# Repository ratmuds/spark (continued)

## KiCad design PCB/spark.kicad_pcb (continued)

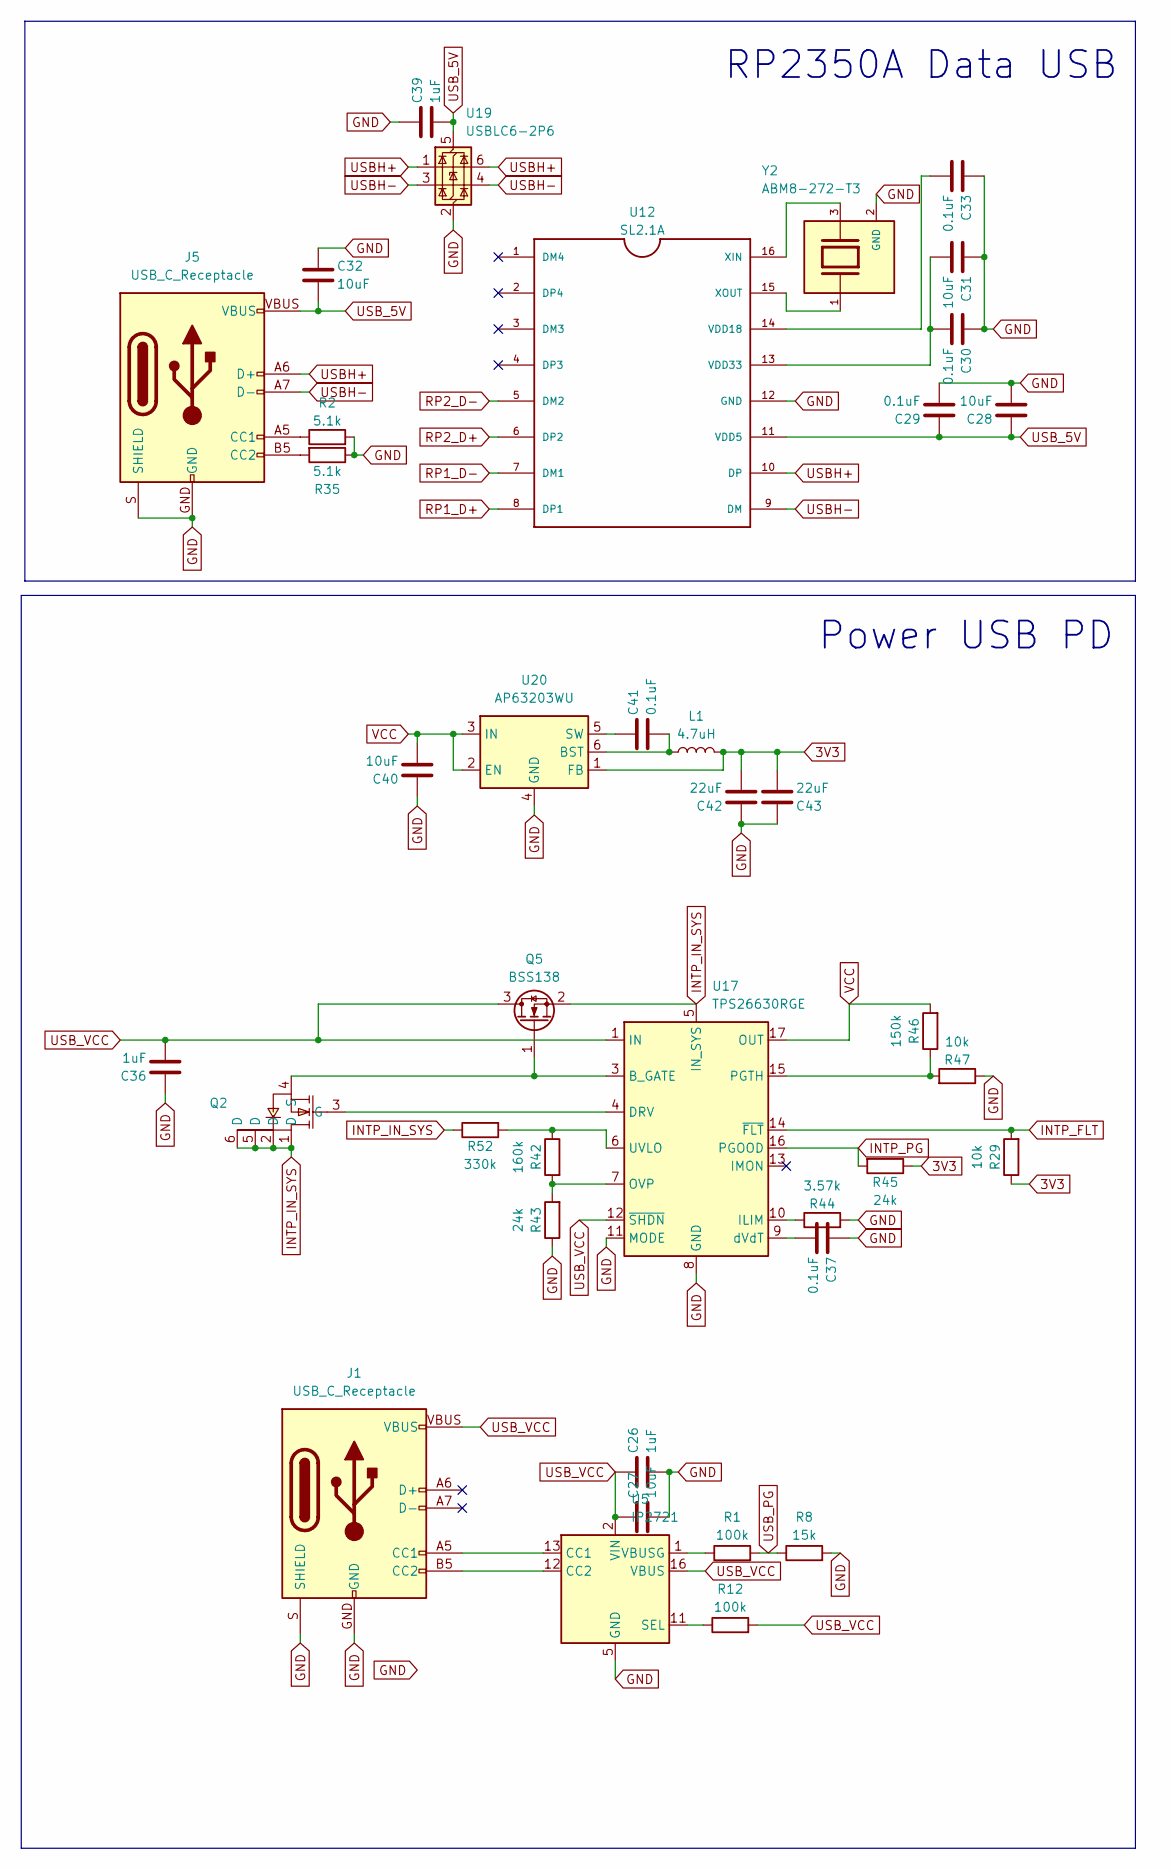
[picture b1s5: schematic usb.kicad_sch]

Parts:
C26, C36, C39: 1uF; C_0402_1005Metric; MPN CL05A105KA5NQNC
C27, C28, C31, C32, C40: 10uF; C_0805_2012Metric; MPN CL21A106KAYNNNE
C29, C30, C33, C37, C41: 0.1uF; C_0402_1005Metric; MPN CL05B104KB54PNC
C42, C43: 22uF; C_0805_2012Metric; MPN CL21A226MAQNNNE
J1, J5: USB_C_Receptacle; USB-C_16; MPN TYPE-C-31-M-12
L1: 4.7uH; L_TechFuse_SL0420; MPN SRP4020TA-4R7M
Q2: STT6N3LLH6_C3021100; SOT-23-6_L2.9-W1.6-P0.95-LS2.8-BR; MPN STT6N3LLH6; LCSC Part C3021100
Q5: BSS138; SOT-23; MPN BSS138
R1, R12: 100k; R_0402_1005Metric; MPN 0402WGF1003TCE
R2, R35: 5.1k; R_0402_1005Metric; MPN 0402WGF5101TCE
R8: 15k; R_0402_1005Metric; MPN 0402WGF1502TCE
R29, R47: 10k; R_0402_1005Metric; MPN 0402WGF1002TCE
R42: 160k; R_0603_1608Metric; MPN 0603WAF1603T5E
R43, R45: 24k; R_0402_1005Metric; MPN 0402WGF2402TCE
R44: 3.57k; R_0603_1608Metric; MPN 0603WAF3601T5E
R46: 150k; R_0402_1005Metric; MPN 0402WGF1503TCE
R52: 330k; R_0402_1005Metric; MPN 0402WGF3303TCE
U5: IP2721; TSSOP-16_4.4x5mm_P0.65mm; MPN IP2721
U12: SL2.1A; SO16; MPN SL2.1A
U17: TPS26630RGE; Texas_RGE0024H_VQFN-24-1EP_4x4mm_P0.5mm_EP2.7x2.7mm_Thermal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; MPN TPS26630RGER
U19: USBLC6-2P6; SOT-666; MPN USBLC6-2P6
U20: AP63203WU; TSOT-23-6; MPN AP63203WU-7
Y2: ABM8-272-T3; XTAL_ABM8-272-T3; PARTREV 07-29-20

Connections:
3V3: C42.1, C43.1, L1.2, R29.1, R45.1, U20.1 (FB); also elsewhere on the board
GND: C26.1, C27.1, C28.1, C29.1, C30.2, C31.2, C32.2, C33.2, C36.2, C37.2, C39.2, C40.2, C42.2, C43.2, J1.GND, J1.S (SHIELD), J5.GND, J5.S (SHIELD), R2.2, R8.2, R35.1, R43.1, R44.2, R47.1, U5.5 (GND), U12.12 (GND), U17.8 (GND), U17.11 (MODE), U17.25 (GND), U19.2 (GND), U20.4 (GND), Y2.2 (GND), Y2.4 (GND); also elsewhere on the board
INTP_FLT: R29.2, U17.14 (~FLT); also elsewhere on the board
INTP_IN_SYS: Q2.1 (D), Q2.2 (D), Q2.5 (D), Q2.6 (D), Q5.2 (S), R52.1, U17.5 (IN_SYS)
INTP_PG: R45.2, U17.16 (PGOOD)
unnamed: J1.A5 (CC1), U5.13 (CC1)
unnamed: J1.B5 (CC2), U5.12 (CC2)
unnamed: J5.A5 (CC1), R2.1
unnamed: J5.B5 (CC2), R35.2
unnamed: Q2.3 (G), U17.4 (DRV)
unnamed: Q2.4 (S), Q5.1 (G), U17.3 (B_GATE)
unnamed: R12.1, U5.11 (SEL)
unnamed: R1.1, U5.1 (VBUSG)
unnamed: C33.1, U12.14 (VDD18)
unnamed: C30.1, C31.1, U12.13 (VDD33)
unnamed: U12.16 (XIN), Y2.3
unnamed: U12.15 (XOUT), Y2.1
unnamed: R44.1, U17.10 (ILIM)
unnamed: R42.2, R43.2, U17.7 (OVP)
unnamed: R46.1, R47.2, U17.15 (PGTH)
unnamed: R42.1, R52.2, U17.6 (UVLO)
unnamed: C37.1, U17.9 (dVdT)
unnamed: C41.1, L1.1, U20.6 (BST)
unnamed: C41.2, U20.5 (SW)
RP1_D+: U12.8 (DP1); also elsewhere on the board
RP1_D-: U12.7 (DM1); also elsewhere on the board
RP2_D+: U12.6 (DP2); also elsewhere on the board
RP2_D-: U12.5 (DM2); also elsewhere on the board
USBH+: J5.A6 (D+), J5.B6 (D+), U12.10 (DP), U19.1 (I/O1), U19.6 (I/O1)
USBH-: J5.A7 (D-), J5.B7 (D-), U12.9 (DM), U19.3 (I/O2), U19.4 (I/O2)
USB_5V: C28.2, C29.2, C32.1, C39.1, J5.VBUS, U12.11 (VDD5), U19.5 (VBUS)
USB_PG: R1.2, R8.1; also elsewhere on the board
USB_VCC: C26.2, C27.2, C36.1, J1.VBUS, Q5.3 (D), R12.2, U5.2 (VIN), U5.16 (VBUS), U17.1 (IN), U17.2 (IN), U17.12 (~SHDN)
VCC: C40.1, R46.2, U17.17 (OUT), U17.18 (OUT), U20.2 (EN), U20.3 (IN); also elsewhere on the board

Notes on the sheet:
Power USB PD
RP2350A Data USB

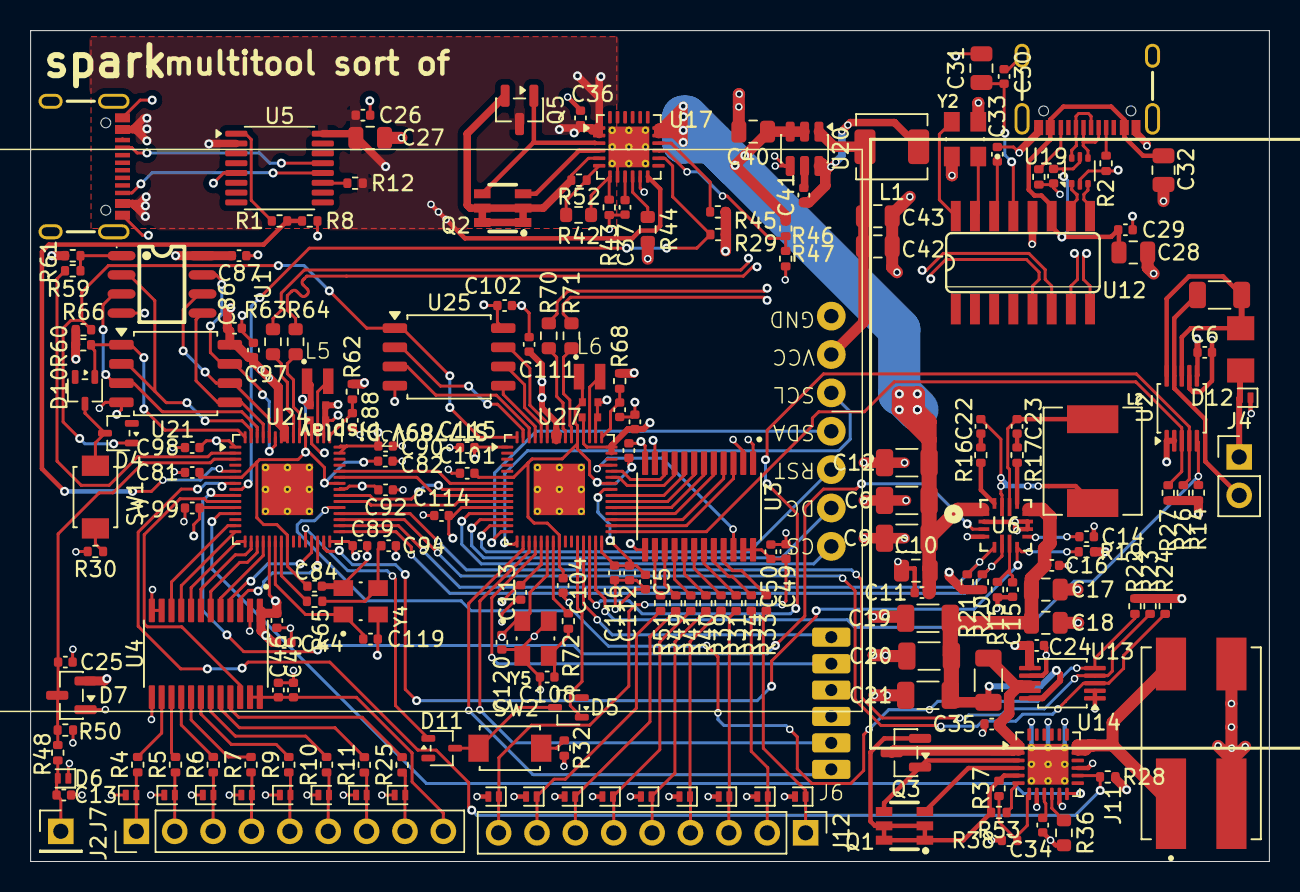
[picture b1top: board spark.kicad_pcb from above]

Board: 4 copper layers, 82.0 x 55.0 mm, 202 parts (0 on the bottom side), 170 nets.

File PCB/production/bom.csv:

Designator,Footprint,Quantity,Value,LCSC Part #
C10,0805,1,22uF 25V,CL21A226MAQNNNE
"C100, C103, C104, C105, C82, C83, C85, C88",0402,8,4.7uF,CL05A475MP5NRNC
"C101, C102, C106, C110, C111, C112, C113, C114, C115, C116, C24, C25, C29, C30, C33, C34, C37, C41, C44, C45, C49, C5, C81, C84, C86, C87, C89, C90, C91, C92, C97, C98, C99",0402,33,0.1uF,CL05B104KB54PNC
"C108, C119, C120, C94",0402,4,15pF,0402CG150J500NT
"C11, C16, C22, C23, C6",0402,5,0.1uF 25V,CL05B104KB54PNC
"C12, C19, C20, C21, C8, C9",1206,6,47uF 25V,C3216X5R1E476MTJ00E
C13,0402,1,100pF C0G/NP0,0402CG101J500NT
"C14, C26, C35, C36, C39, C46, C50",0402,7,1uF,CL05A105KA5NQNC
C15,0402,1,22nF,0402B223K500NT
"C17, C18",0805,2,10uF 25V,CL21A106KAYNNNE
"C27, C28, C31, C32, C40",0805,5,10uF,CL21A106KAYNNNE
"C42, C43",0805,2,22uF,CL21A226MAQNNNE
"D10, D11, D4, D5",SOT-323_SC-70,4,BAT54W,BAT54W
"D12, D13, D14, D15, D16, D17, D18, D19, D20, D21, D22, D23, D24, D25, D26, D27, D28, D29, D6",D_SOD-882,19,PESD5V0U1BL,PESD5V0U1BL
D7,SOT-23,1,BAT54S,BAT54S
F1,1206,1,6V/0.5A/1A,1206L050YR
"J1, J5",USB-C_16,2,USB_C_Receptacle,TYPE-C-31-M-12
J11,WAGO_2060-452_998-404,1,Power Supply Out,2060-452/998-404
L1,L_TechFuse_SL0420,1,4.7uH,SRP4020TA-4R7M
L2,IND_SPM6530T-4R7M,1,4.7uH,SPM6530T-4R7M
"L5, L6",AOTA-B201610S3R3-101-T,2,3.3uH,AOTA-B201610S3R3-101-T
"Q1, Q2",SOT-23-6_L2.9-W1.6-P0.95-LS2.8-BR,2,STT6N3LLH6_C3021100,C3021100
"Q3, Q5",SOT-23,2,BSS138,BSS138
"R1, R12, R19, R24, R27",0402,5,100k,0402WGF1003TCE
"R10, R11, R25, R31, R33, R34, R39, R4, R40, R41, R49, R5, R51, R6, R7, R9",0402,16,47,0402WGF470JTCE
"R14, R20, R21, R22, R23, R26",0402,6,4.7k,0402WGF4701TCE
R15,0402,1,22k,0402WGF2202TCE
"R16, R17, R59",0402,3,0,0402WGF0000TCE
"R18, R3",1206,2,20m 1W,RLS12FTCR020
"R2, R35",0402,2,5.1k,0402WGF5101TCE
"R28, R29, R47, R50, R61",0402,5,10k,0402WGF1002TCE
"R30, R32, R65, R72",0402,4,1k,0402WGF1001TCE
R36,0603,1,6.2k,0603WAF6201T5E
R37,0402,1,470k,0402WGF4703TCE
"R38, R43, R45",0402,3,24k,0402WGF2402TCE
R42,0603,1,160k,0603WAF1603T5E
R44,0603,1,3.57k,0603WAF3601T5E
R46,0402,1,150k,0402WGF1503TCE
R48,0402,1,8.2k,0402WGF8201TCE
R52,0402,1,330k,0402WGF3303TCE
R53,0402,1,300k,0402WGF3003TCE
"R62, R68",0402,2,33,0402WGF330JTCE
"R63, R64, R70, R71",0603,4,27,0603WAF270JT5E
R8,0402,1,15k,0402WGF1502TCE
"SW1, SW2",SW_TS-1088-AR02016,2,SW_Push,TS-1088-AR02016
U1,SOP-8_L4.9-W3.9-P1.27-LS6.0-BL,1,APS6404L-SQN-SN,C5360304
U12,SO16,1,SL2.1A,SL2.1A
"U13, U2",TSSOP-10_3x3mm_P0.5mm,2,INA226,INA226AIDGSR
"U14, U17",Texas_RGE0024H_VQFN-24-1EP_4x4mm_P0.5mm_EP2.7x2.7mm_ThermalVias,2,TPS26630RGE,TPS26630RGER
U19,SOT-666,1,USBLC6-2P6,USBLC6-2P6
U20,TSOT-23-6,1,AP63203WU,AP63203WU-7
"U21, U25",SOIC-8_5.3x5.3mm_P1.27mm,2,W25Q128JVS,W25Q128JVSIQ
"U24, U27",QFN-60-1EP_7x7mm_P0.4mm_EP3.4x3.4mm_ThermalVias,2,RP2350A,RP2350A
"U3, U4",SOP65P640X120-24N,2,SN74LVC8T245PWR,C27643
U5,TSSOP-16_4.4x5mm_P0.65mm,1,IP2721,IP2721
U6,QFN-16_MP8859_00_MNP,1,MP8859GQ-0000-Z,MP8859GQ-0000-Z 
"Y2, Y4, Y5",XTAL_ABM8-272-T3,3,ABM8-272-T3,ABM8-272-T3

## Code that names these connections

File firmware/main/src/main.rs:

#![no_std]
#![no_main]

use defmt::*;
use defmt_rtt as _;
use embedded_hal::delay::DelayNs;
use embedded_hal::digital::OutputPin;
#[cfg(target_arch = "riscv32")]
use panic_halt as _;
#[cfg(target_arch = "arm")]
use panic_probe as _;

// Alias for our HAL crate
use hal::entry;
use hal::fugit::RateExtU32;
use embedded_hal::spi::SpiBus;
use hal::clocks::Clock;


#[cfg(rp2350)]
use rp235x_hal as hal;

#[cfg(rp2040)]
use rp2040_hal as hal;

// use bsp::entry;
// use bsp::hal;
// use rp_pico as bsp;

/// The linker will place this boot block at the start of our program image. We
/// need this to help the ROM bootloader get our code up and running.
/// Note: This boot block is not necessary when using a rp-hal based BSP
/// as the BSPs already perform this step.
#[unsafe(link_section = ".boot2")]
#[used]
#[cfg(rp2040)]
pub static BOOT2: [u8; 256] = rp2040_boot2::BOOT_LOADER_W25Q080;

/// Tell the Boot ROM about our application
#[unsafe(link_section = ".start_block")]
#[used]
#[cfg(rp2350)]
pub static IMAGE_DEF: hal::block::ImageDef = hal::block::ImageDef::secure_exe();

/// External high-speed crystal on the Raspberry Pi Pico 2 board is 12 MHz.
/// Adjust if your board has a different frequency
const XTAL_FREQ_HZ: u32 = 12_000_000u32;

/// Entry point to our bare-metal application.
///
/// The `#[hal::entry]` macro ensures the Cortex-M start-up code calls this function
/// as soon as all global variables and the spinlock are initialised.
///
/// The function configures the rp2040 and rp235x peripherals, then toggles a GPIO pin in
/// an infinite loop. If there is an LED connected to that pin, it will blink.
#[entry]
fn main() -> ! {
    info!("Program start");
    // Grab our singleton objects
    let mut pac = hal::pac::Peripherals::take().unwrap();

    // Set up the watchdog driver - needed by the clock setup code
    let mut watchdog = hal::Watchdog::new(pac.WATCHDOG);

    // Configure the clocks
    let clocks = hal::clocks::init_clocks_and_plls(
        XTAL_FREQ_HZ,
        pac.XOSC,
        pac.CLOCKS,
        pac.PLL_SYS,
        pac.PLL_USB,
        &mut pac.RESETS,
        &mut watchdog,
    )
    .unwrap();

    #[cfg(rp2040)]
    let mut timer = hal::Timer::new(pac.TIMER, &mut pac.RESETS, &clocks);

    #[cfg(rp2350)]
    let mut timer = hal::Timer::new_timer0(pac.TIMER0, &mut pac.RESETS, &clocks);

    // The single-cycle I/O block controls our GPIO pins
    let sio = hal::Sio::new(pac.SIO);

    // Set the pins to their default state
    let pins = hal::gpio::Pins::new(
        pac.IO_BANK0,
        pac.PADS_BANK0,
        sio.gpio_bank0,
        &mut pac.RESETS,
    );

    // SPI Slave Configuration
    // SPI1: RX=24, CS=25, SCK=26, TX=27
    let spi = hal::Spi::<_, _, _, 8>::new(pac.SPI1, (
        pins.gpio27.into_function::<hal::gpio::FunctionSpi>(), // TX
        pins.gpio24.into_function::<hal::gpio::FunctionSpi>(), // RX
        pins.gpio26.into_function::<hal::gpio::FunctionSpi>(), // SCK
    ));

    let mut spi = spi.init(
        &mut pac.RESETS,
        clocks.peripheral_clock.freq(),
        1_000_000_u32.Hz(), // 1 MHz - matches master
        &embedded_hal::spi::Mode {
            polarity: embedded_hal::spi::Polarity::IdleHigh,
            phase: embedded_hal::spi::Phase::CaptureOnSecondTransition,
        },
    );

    let _cs_pin = pins.gpio25.into_floating_input();

    // Initialize GPIO pins 10-17 as logic analyzer inputs
    let _g10 = pins.gpio10.into_floating_input();
    let _g11 = pins.gpio11.into_floating_input();
    let _g12 = pins.gpio12.into_floating_input();
    let _g13 = pins.gpio13.into_floating_input();
    let _g14 = pins.gpio14.into_floating_input();
    let _g15 = pins.gpio15.into_floating_input();
    let _g16 = pins.gpio16.into_floating_input();
    let _g17 = pins.gpio17.into_floating_input();

    let mut capture_buffer = [0u8; 1000];

    loop {
        let mut cmd_buf = [0u8; 1];
        let mut response_buf = [0u8; 1];

        // Read SPI command
        if let Ok(_) = spi.read(&mut cmd_buf) {
            let cmd = cmd_buf[0];
            
            // CMD = 0x01 (Start Capture)
            if cmd == 0x01 {
                // Actually read GPIO as fast as possible in a tight CPU loop
                // Pins 10-17 are correctly aligned if we shift by 10 maybe
                for _i in 0..100 {
                    // Loop unrolling for maximum CPU capture speed
                    capture_buffer[0] = (unsafe { (*hal::pac::SIO::PTR).gpio_in() }.read().bits() >> 10) as u8;
                    capture_buffer[1] = (unsafe { (*hal::pac::SIO::PTR).gpio_in() }.read().bits() >> 10) as u8;
                    capture_buffer[2] = (unsafe { (*hal::pac::SIO::PTR).gpio_in() }.read().bits() >> 10) as u8;
                    capture_buffer[3] = (unsafe { (*hal::pac::SIO::PTR).gpio_in() }.read().bits() >> 10) as u8;
                    capture_buffer[4] = (unsafe { (*hal::pac::SIO::PTR).gpio_in() }.read().bits() >> 10) as u8;
                    capture_buffer[5] = (unsafe { (*hal::pac::SIO::PTR).gpio_in() }.read().bits() >> 10) as u8;
                    capture_buffer[6] = (unsafe { (*hal::pac::SIO::PTR).gpio_in() }.read().bits() >> 10) as u8;
                    capture_buffer[7] = (unsafe { (*hal::pac::SIO::PTR).gpio_in() }.read().bits() >> 10) as u8;
                    capture_buffer[8] = (unsafe { (*hal::pac::SIO::PTR).gpio_in() }.read().bits() >> 10) as u8;
                    capture_buffer[9] = (unsafe { (*hal::pac::SIO::PTR).gpio_in() }.read().bits() >> 10) as u8;
                }
                
                // return length or something
                response_buf[0] = (capture_buffer.len() & 0xFF) as u8;
                let _ = spi.write(&response_buf);
            }
        }
    }
}

/// Program metadata for `picotool info`
#[unsafe(link_section = ".bi_entries")]
#[used]
pub static PICOTOOL_ENTRIES: [hal::binary_info::EntryAddr; 5] = [
    hal::binary_info::rp_cargo_bin_name!(),
    hal::binary_info::rp_cargo_version!(),
    hal::binary_info::rp_program_description!(c"Blinky Example"),
    hal::binary_info::rp_cargo_homepage_url!(),
    hal::binary_info::rp_program_build_attribute!(),
];

// End of file

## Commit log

2026-04-18 init repo
2026-04-18 Fix MPN number, adjust footprint, production files
2026-04-20 Secondary MCU untested firmware
2026-04-20 Main MCU testing firmware
2026-04-20 Add case and case renders
2026-04-20 Add BOM and screenshots and cleanup. Updated PCB for fixed footprint for capacitor.
